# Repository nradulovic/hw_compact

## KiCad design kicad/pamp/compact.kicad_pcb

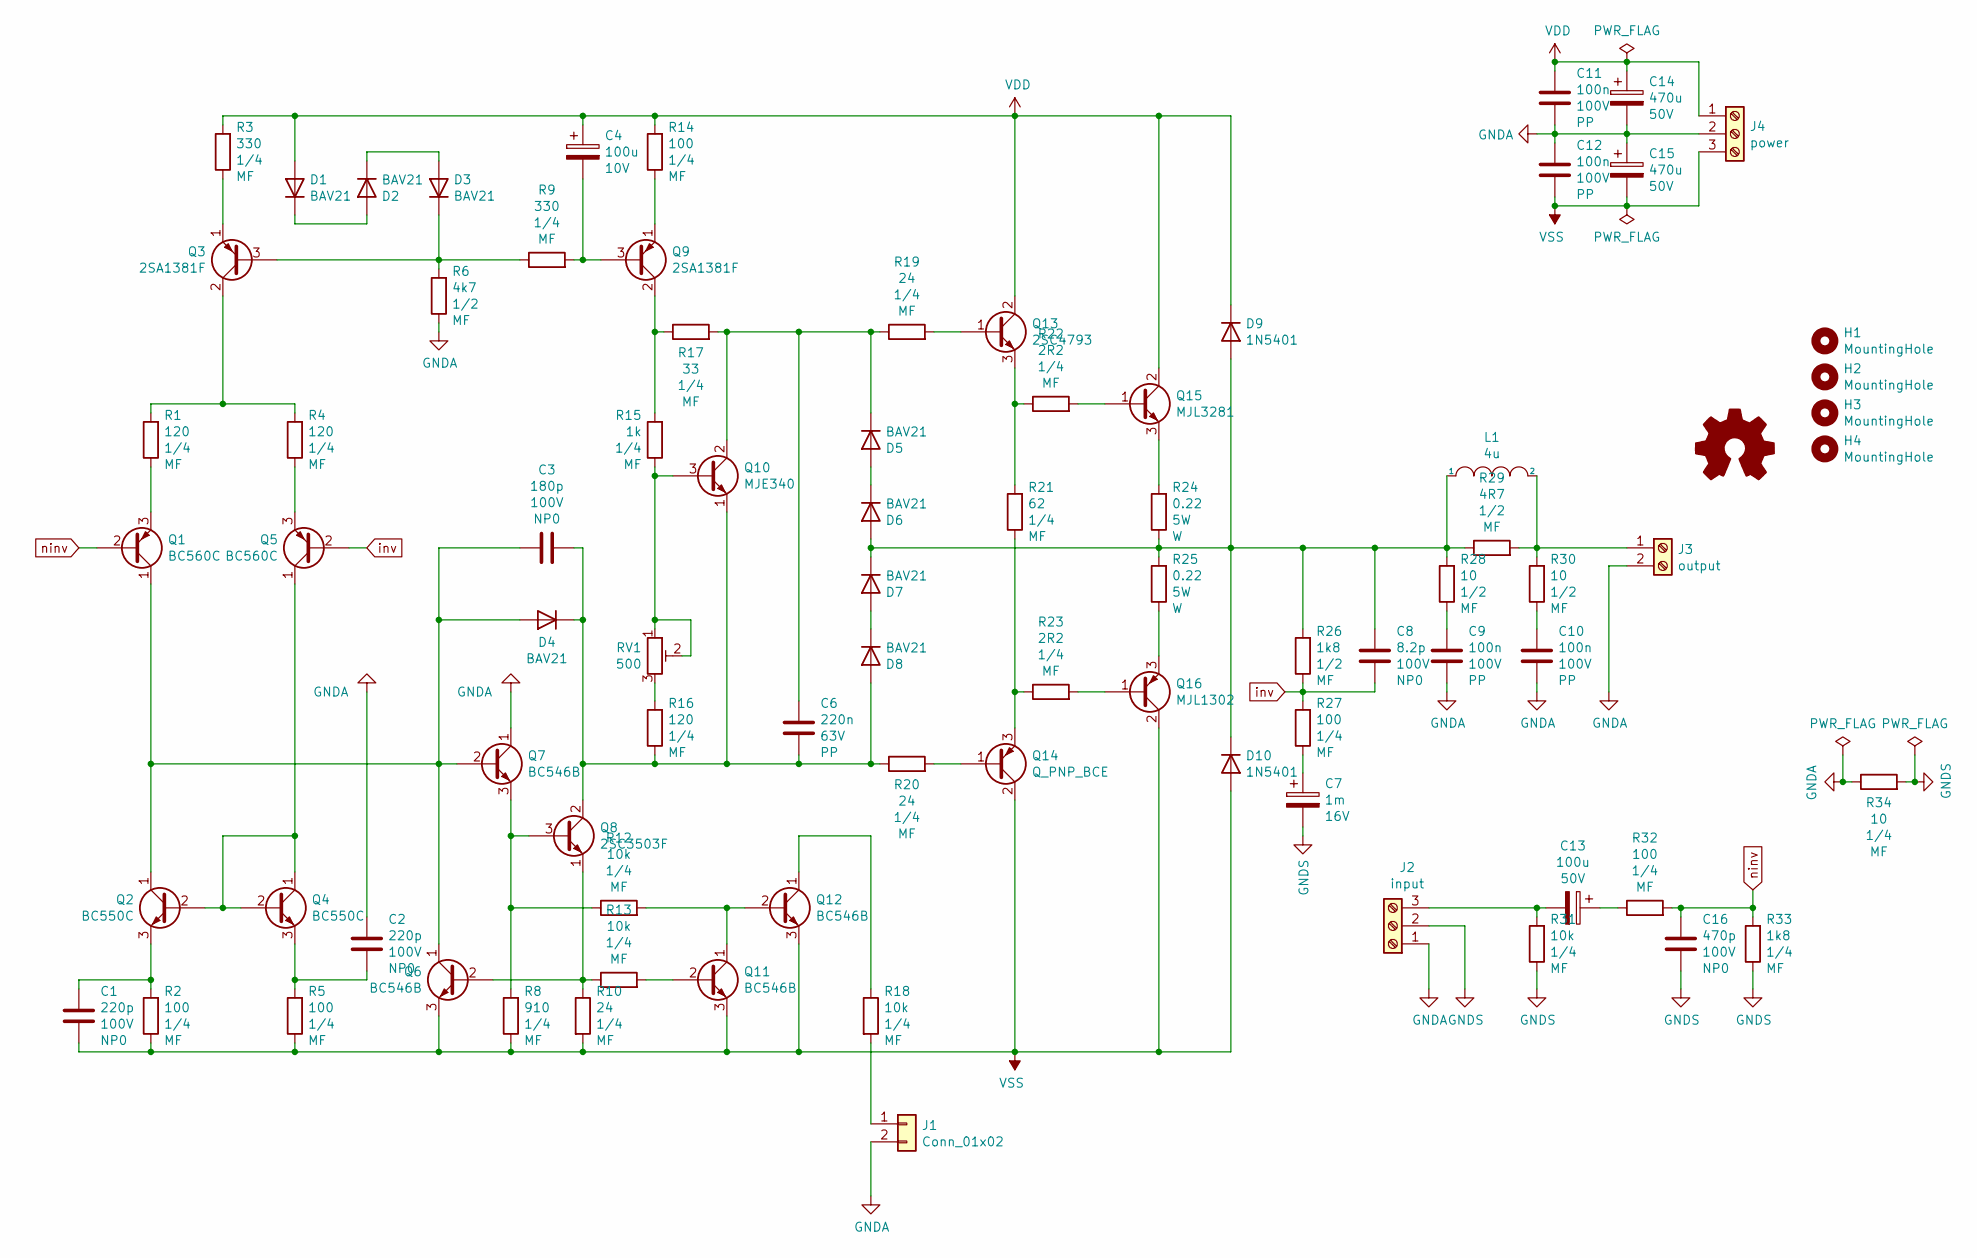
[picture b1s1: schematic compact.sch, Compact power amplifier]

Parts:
C1, C2: 220p; C_Disc_D8.0mm_W2.5mm_P5.00mm; Voltage 100V
C3: 180p; C_Disc_D8.0mm_W2.5mm_P5.00mm; Voltage 100V
C4: 100u; CP_Radial_D8.0mm_P2.50mm; Voltage 10V
C6: 220n; C_Rect_L7.2mm_W4.5mm_P5.00mm_FKS2_FKP2_MKS2_MKP2; Voltage 63V
C7: 1m; CP_Radial_D10.0mm_P3.50mm; Voltage 16V
C8: 8.2p; C_Disc_D3.0mm_W2.0mm_P2.50mm; Voltage 100V
C9, C10, C11, C12: 100n; C_Rect_L7.2mm_W5.5mm_P5.00mm_FKS2_FKP2_MKS2_MKP2; Voltage 100V
C13: 100u; CP_Radial_D10.0mm_P3.50mm; Voltage 50V
C14, C15: 470u; CP_Radial_D10.0mm_P3.50mm; Voltage 50V
C16: 470p; C_Disc_D8.0mm_W2.5mm_P5.00mm; Voltage 100V
D1, D2, D3, D4, D5, D6, D7, D8: BAV21; D_DO-41_SOD81_P7.62mm_Horizontal
D9, D10: 1N5401; D_DO-201AD_P15.24mm_Horizontal
H1, H2, H3, H4: MountingHole; MountingHole_3.2mm_M3_Pad
J1: Conn_01x02; PinHeader_1x02_P2.54mm_Vertical
J2: input; TerminalBlock_Phoenix_PT-1,5-3-3.5-H_1x03_P3.50mm_Horizontal
J3: output; PhoenixContact_MCV_1,5_2-G-3.81_1x02_P3.81mm_Vertical
J4: power; PhoenixContact_MCV_1,5_3-G-3.81_1x03_P3.81mm_Vertical
L1: 4u; L_Axial_L29.9mm_D14.0mm_P7.62mm_Vertical_Vishay_IHA-105
LOGO1: Logo_Open_Hardware_Small; KiCad-Logo_5mm_Copper
Q1, Q5: BC560C; TO-92L_Inline_Wide
Q2, Q4: BC550C; TO-92L_Inline_Wide
Q3: 2SA1381F; TO-126-3_Vertical
Q6, Q7, Q11, Q12: BC546B; TO-92L_Inline_Wide
Q8: 2SC3503F; TO-126-3_Horizontal_TabDown
Q9: 2SA1381F; TO-126-3_Horizontal_TabDown
Q10: MJE340; TO-126-3_Vertical
Q13: 2SC4793; TO-220-3_Vertical
Q14: Q_PNP_BCE; TO-220-3_Vertical
Q15: MJL3281; TO-264-3_Vertical
Q16: MJL1302; TO-264-3_Vertical
R1, R4, R16: 120; R_Axial_DIN0207_L6.3mm_D2.5mm_P10.16mm_Horizontal
R2, R5, R14, R27, R32: 100; R_Axial_DIN0207_L6.3mm_D2.5mm_P10.16mm_Horizontal
R3, R9: 330; R_Axial_DIN0207_L6.3mm_D2.5mm_P10.16mm_Horizontal
R6: 4k7; R_Axial_DIN0411_L9.9mm_D3.6mm_P12.70mm_Horizontal
R8: 910; R_Axial_DIN0207_L6.3mm_D2.5mm_P10.16mm_Horizontal
R10, R19, R20: 24; R_Axial_DIN0207_L6.3mm_D2.5mm_P10.16mm_Horizontal
R12, R13, R18, R31: 10k; R_Axial_DIN0207_L6.3mm_D2.5mm_P10.16mm_Horizontal
R15: 1k; R_Axial_DIN0207_L6.3mm_D2.5mm_P10.16mm_Horizontal
R17: 33; R_Axial_DIN0207_L6.3mm_D2.5mm_P10.16mm_Horizontal
R21: 62; R_Axial_DIN0207_L6.3mm_D2.5mm_P10.16mm_Horizontal
R22, R23: 2R2; R_Axial_DIN0207_L6.3mm_D2.5mm_P10.16mm_Horizontal
R24, R25: 0.22; R_Axial_Power_L20.0mm_W6.4mm_P25.40mm
R26: 1k8; R_Axial_DIN0411_L9.9mm_D3.6mm_P12.70mm_Horizontal
R28, R30: 10; R_Axial_DIN0411_L9.9mm_D3.6mm_P12.70mm_Horizontal
R29: 4R7; R_Axial_DIN0411_L9.9mm_D3.6mm_P12.70mm_Horizontal
R33: 1k8; R_Axial_DIN0207_L6.3mm_D2.5mm_P10.16mm_Horizontal
R34: 10; R_Axial_DIN0207_L6.3mm_D2.5mm_P10.16mm_Horizontal
RV1: 500; Potentiometer_ACP_CA9-V10_Vertical

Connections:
GNDA: C2.2, C9.2, C10.2, C11.2, C12.1, C14.2, C15.1, J1.2, J2.1, J3.2, J4.2, Q7.1 (C), R6.1, R34.1
GNDS: C7.2, C16.1, J2.2, R31.1, R33.1, R34.2
unnamed: C1.2, Q2.3 (E), R2.2
unnamed: C2.1, Q4.3 (E), R5.2
unnamed: C3.1, C6.2, D4.1 (K), D8.2 (A), Q8.2 (C), Q10.1 (E), R16.1, R20.1
unnamed: C3.2, D4.2 (A), Q1.1 (C), Q2.1 (C), Q6.1 (C), Q7.2 (B)
unnamed: C4.2, Q9.3 (B), R9.2
unnamed: C6.1, D5.1 (K), Q10.2 (C), R17.2, R19.1
unnamed: C7.1, R27.1
unnamed: C8.1, D6.2 (A), D7.1 (K), D9.2 (A), D10.1 (K), L1.1, R24.1, R25.2, R26.2, R28.2, R29.1
unnamed: C9.1, R28.1
unnamed: C10.1, R30.1
unnamed: C13.1, R32.1
unnamed: C13.2, J2.3, R31.2
unnamed: D1.1 (K), D2.2 (A)
unnamed: D2.1 (K), D3.2 (A)
unnamed: D3.1 (K), Q3.3 (B), R6.2, R9.1
unnamed: D5.2 (A), D6.1 (K)
unnamed: D7.2 (A), D8.1 (K)
unnamed: J1.1, R18.2
unnamed: J3.1, L1.2, R29.2, R30.2
unnamed: Q1.3 (E), R1.1
unnamed: Q2.2 (B), Q4.1 (C), Q4.2 (B), Q5.1 (C)
unnamed: Q3.1 (E), R3.1
unnamed: Q3.2 (C), R1.2, R4.2
unnamed: Q5.3 (E), R4.1
unnamed: Q6.2 (B), Q8.1 (E), R10.1, R13.1
unnamed: Q7.3 (E), Q8.3 (B), R8.2, R12.1
unnamed: Q9.1 (E), R14.1
unnamed: Q9.2 (C), R15.2, R17.1
unnamed: Q10.3 (B), R15.1, RV1.1, RV1.2
unnamed: Q11.1 (C), Q12.2 (B), R12.2
unnamed: Q11.2 (B), R13.2
unnamed: Q12.1 (C), R18.1
unnamed: Q13.1 (B), R19.2
unnamed: Q13.3 (E), R21.2, R22.1
unnamed: Q14.1 (B), R20.2
unnamed: Q14.3 (E), R21.1, R23.1
unnamed: Q15.1 (B), R22.2
unnamed: Q15.3 (E), R24.2
unnamed: Q16.1 (B), R23.2
unnamed: Q16.3 (E), R25.1
unnamed: R16.2, RV1.3
VDD: C4.1, C11.1, C14.1, D1.2 (A), D9.1 (K), J4.1, Q13.2 (C), Q15.2 (C), R3.2, R14.2
VSS: C1.1, C12.2, C15.2, D10.2 (A), J4.3, Q6.3 (E), Q11.3 (E), Q12.3 (E), Q14.2 (C), Q16.2 (C), R2.1, R5.1, R8.1, R10.2
inv: C8.2, Q5.2 (B), R26.1, R27.2
ninv: C16.2, Q1.2 (B), R32.2, R33.2

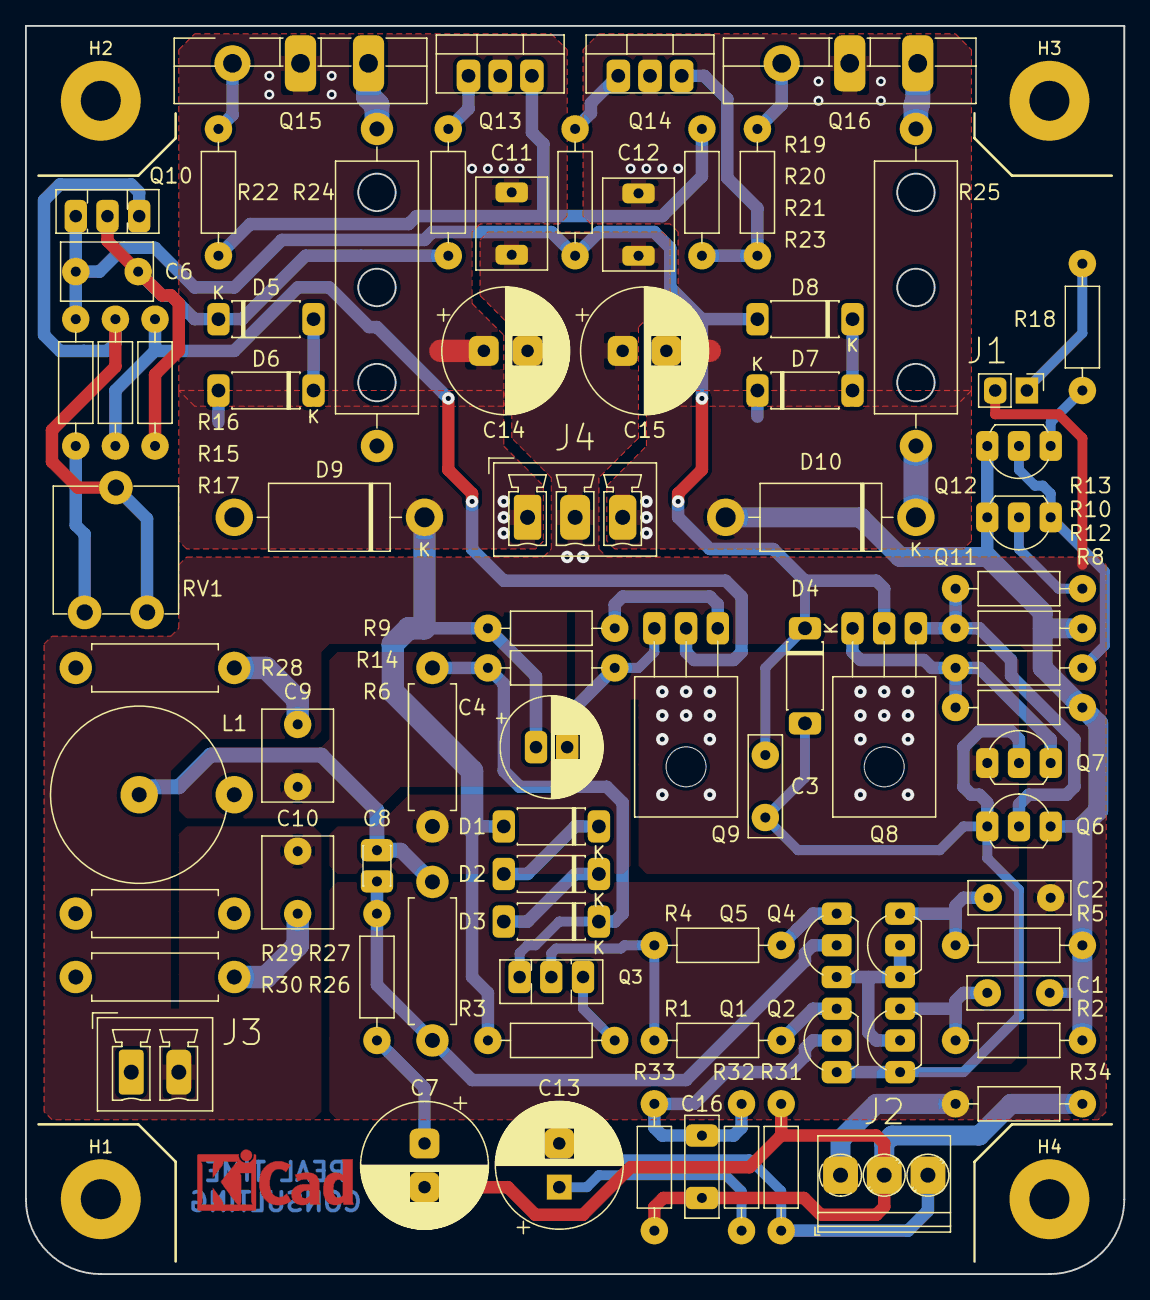
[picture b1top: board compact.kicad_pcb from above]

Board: 2 copper layers, 88.0 x 100.0 mm, 84 parts (0 on the bottom side), 47 nets.

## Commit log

2018-12-07 Added spice simulation files.
2018-12-07 Fixed spice library paths
2018-12-07 Minor schematic rearranging
2018-12-10 Moved spice and kicad projects to their own folders.
2019-01-08 Using modular spice approach
2019-02-24 Added spice library module.
2019-02-24 Old version was enhanced a bit.
2019-02-27 Add License
2019-02-27 Updated .gitignore, vi limiter and MOSFET schematic
2019-03-04 Updated values for PSRR improvement caps
2019-03-05 Added protection pin, AC (gain&PSRR) evaluated
2019-04-15 WIP: Using symmetrical MOSFET design.
2019-04-15 WIP: Started schematic.
2019-04-15 WIP: Schematic is almost complete
2019-04-16 Added all components.
2019-04-16 WIP: Resolving ERC.
2019-04-17 Completed schematic and part placement
2019-04-17 Removed stuff which is not needed in this configuration.
2019-04-18 WIP: Done schematic.
2019-04-26 Schematic was made more simple.
2019-05-01 Schematic was made more simple (ltspice).
2019-05-03 Tweaked OPS protection curve.
2019-05-10 Finished SPICE simulation, Kicad follows the updates
    The VAS standing current was increased from 12mA to 15mA to avoid
    VAS lower transistor switch-off during slewing. The VBE multiplier
    was optimized for lower current-to-voltage dependency by increasing
    collector resistor to 43 ohm. Also, the VBE resistor divider was
    chosen in such way that we get around 8.9mV/C characteristic.
    Kicad schematic was updated according to changes in Spice schematic.
2019-05-16 Updated RC values in AC detection circuit.
2019-07-26 The complete schematic design is almost complete.
2019-07-29 Minimal PCB version.
2019-08-03 First prerelease.
2019-12-18 Cleaned up all variants.
2020-04-22 Renamed LTSpice files.
2020-09-15 Revert "Renamed LTSpice files."
    This reverts commit e81dcb455d8e29956ea19cb673c2dd2f2ab4fe7d.
2020-09-15 Made the compensation scheme much simpler.
2021-03-16 Optimized AC specs
2021-07-24 reducing the complexity
2021-07-25 feat: THD20 .005@16V
2021-07-26 Revert "feat: THD20 .005@16V"
    After evaluating simple architectures it was concluded that this complex
    architecture is not worth it.
    This reverts commit fa6ed1e580e39e242b81db925e514dbd501194ff.
2021-07-26 feat: THD1.002@16V
2021-07-28 feat: fast impulse response
2021-08-04 feat: impulse like topology
2021-08-18 feat: project organization
